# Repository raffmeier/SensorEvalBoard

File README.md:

# Sensor Evaluation Board

## Overview

These are the KiCad files for a simple sensor evaluation board. It features an STM32F4 MCU, an IMU (BMI088), a magnetometer (LIS3MDLTR) and a barometer (BMP390). All sensors are connected to the same I2C interface on the microcontroller. The board is powered by the USB-C port and can be programmed via the SWD pins which are placed on the connector to interface with an ST-LINK V3MINIE (UART1 is routed to STLINK). Additionaly the STM32 could be programmed via the USB cable in DFU mode by setting the BOOT0 jumper to high. The board features some extra GPIO (e.g. the sensor I2C bus, UART2) headers and two controllable LEDs.

## Pictures

PCB after SMD soldering.

Layout of the PCB. Build-Up: SGN-GND-3V3-SGN

## BOM
- STM32F401RCT6 (1)
- BMI088 (1)
- LIS3MDLTR (1)
- BMP390 (1)
- 10p 0603 cap (2)
- 10n 0603 cap (1)
- 100n 0603 cap (14)
- 1u 0603 cap (4)
- 4.7u 0805 cap (2)
- 10u 0805 cap (1)
- Red SMD LED 0603 (3)
- Ferrite bead 600 ohm 0805 (e.g. HZ0805E601R-10) (1)
- 100 resistor 0603 (1)
- 510 resistor 0603 (3)
- 5.1k resistor (4)
- 10k resistor 0603 (1)
- USB-C USB2.0 receptacle (e.g. USB4105-GF-A) (1)
- FTSH-107-01-L-DV-KCONN HEADER SMD 14POS 1.27MM Samtec Inc. (1)
- USB TVS diode STMicroelectronics USBLC6-2SC6 (1)
- Linear regulator SOT23-5 (e.g. MIC5504-3.3YM5-TR) (1)
- 16MHz oscillator TSX-3225 16.0000MF09Z-AC0 (1)

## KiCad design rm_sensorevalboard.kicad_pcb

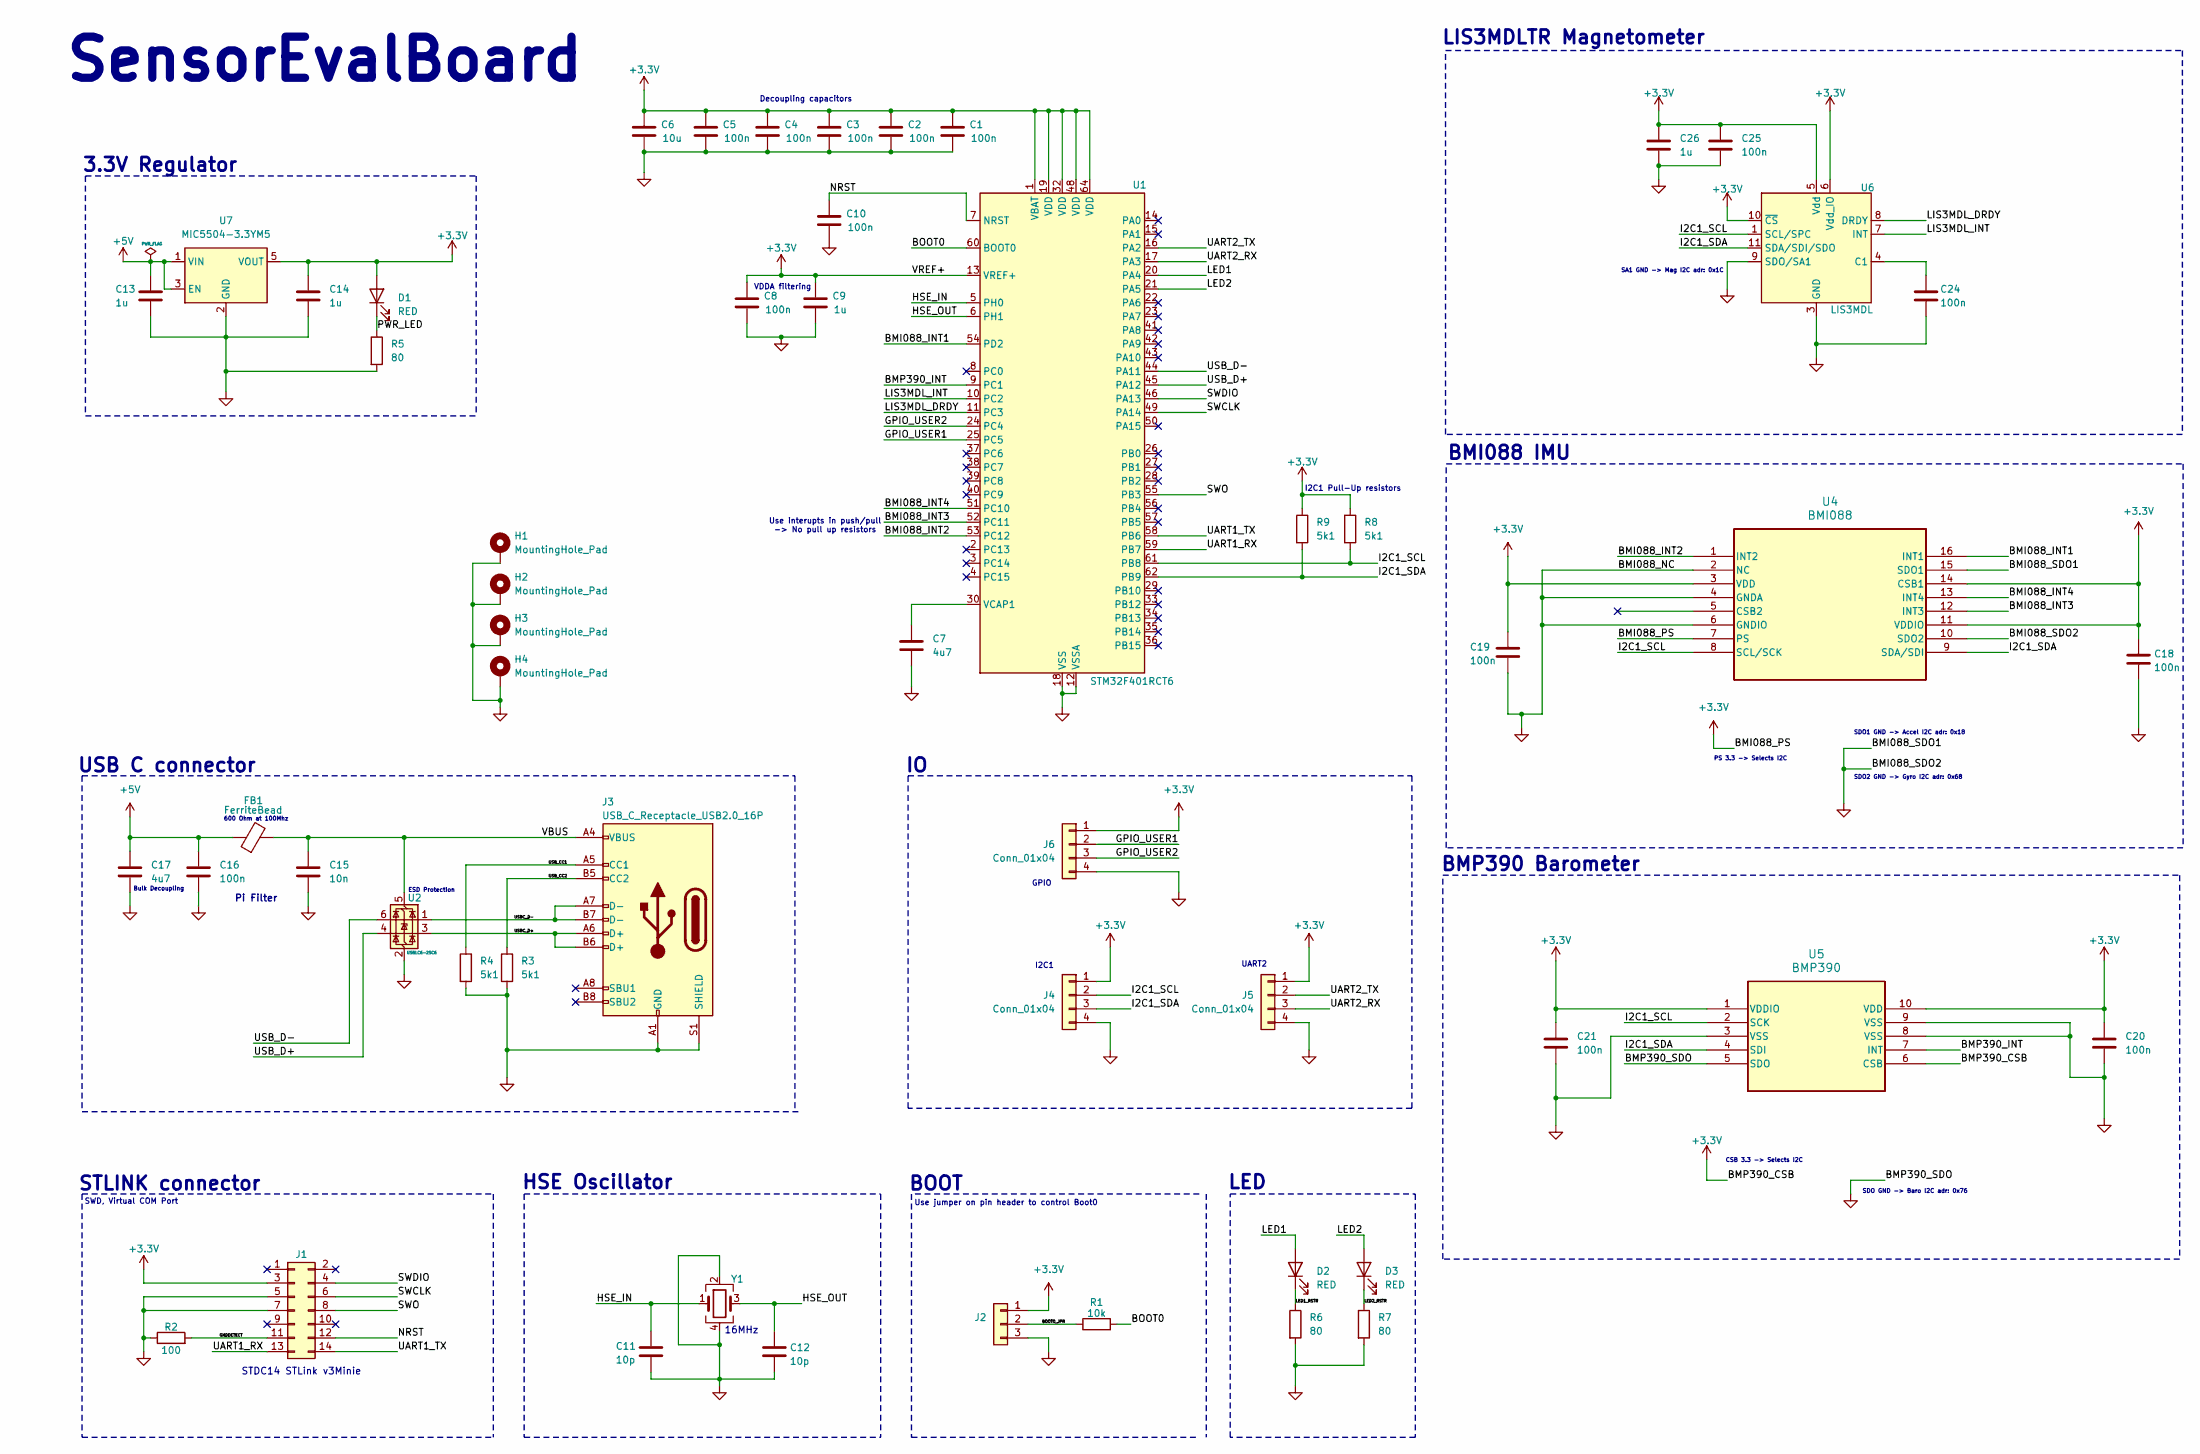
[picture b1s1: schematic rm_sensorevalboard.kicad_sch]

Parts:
C1, C2, C3, C4, C5, C8, C10, C16, C18, C19, C20, C21, C24, C25: 100n; C_0603_1608Metric
C6: 10u; C_0805_2012Metric
C7, C17: 4u7; C_0805_2012Metric
C9, C13, C14, C26: 1u; C_0603_1608Metric
C11, C12: 10p; C_0603_1608Metric
C15: 10n; C_0603_1608Metric
D1, D2, D3: RED; LED_0603_1608Metric; LCSC Part # C2286
FB1: FerriteBead; L_0805_2012Metric; LCSC Part # C1017
H1, H2, H3, H4: MountingHole_Pad; MountingHole_3.2mm_M3_Pad_Via
J1: Conn_02x07_Odd_Even; SAMTEC_FTSH-107-01-F-DV-K; LCSC Part # C7465995
J2: Conn_01x03; PinHeader_1x03_P2.54mm_Vertical
J3: USB_C_Receptacle_USB2.0_16P; USB_C_Receptacle_G-Switch_GT-USB-7010ASV; LCSC Part # C393939
J4, J5, J6: Conn_01x04; PinHeader_1x04_P2.54mm_Vertical
R1: 10k; R_0603_1608Metric
R2: 100; R_0603_1608Metric
R3, R4, R8, R9: 5k1; R_0603_1608Metric
R5, R6, R7: 80; R_0603_1608Metric
U1: STM32F401RCT6; LQFP-64_10x10mm_P0.5mm; LCSC Part # C74524
U2: USBLC6-2SC6; SOT-23-6
U4: BMI088; QFN_BMI085_BOS; LCSC Part # C194919
U5: BMP390; LCSC Part # C2684802
U6: LIS3MDL; LGA-12_2x2mm_P0.5mm
U7: MIC5504-3.3YM5; SOT-23-5
Y1: Crystal_GND24; Crystal_SMD_3225-4Pin_3.2x2.5mm; LCSC Part # C13738

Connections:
+3.3V: C1.1, C2.1, C3.1, C4.1, C5.1, C6.1, C8.1, C9.1, C14.1, C18.1, C19.1, C20.1, C21.1, C25.1, C26.1, D1.2 (A), J1.3, J2.1, J4.1, J5.1, J6.1, R8.1, R9.1, U1.1 (VBAT), U1.13 (VREF+), U1.19 (VDD), U1.32 (VDD), U1.48 (VDD), U1.64 (VDD), U4.3 (VDD), U4.7 (PS), U4.11 (VDDIO), U4.14 (CSB1), U5.1 (VDDIO), U5.6 (CSB), U5.10 (VDD), U6.5 (Vdd), U6.6 (Vdd_IO), U6.10 (~CS), U7.5 (VOUT)
+5V: C13.1, C16.1, C17.1, FB1.1, U7.1 (VIN), U7.3 (EN)
/BMI088_INT1: U1.54 (PD2), U4.16 (INT1)
/BMI088_INT2: U1.53 (PC12), U4.1 (INT2)
/BMI088_INT3: U1.52 (PC11), U4.12 (INT3)
/BMI088_INT4: U1.51 (PC10), U4.13 (INT4)
/BMP390_INT: U1.9 (PC1), U5.7 (INT)
/BOOT0: R1.2, U1.60 (BOOT0)
/BOOT0_JPR: J2.2, R1.1
/GNDDETECT: J1.11, R2.2
/GPIO_USER1: J6.2, U1.25 (PC5)
/GPIO_USER2: J6.3, U1.24 (PC4)
/HSE_IN: C11.1, U1.5 (PH0), Y1.1
/HSE_OUT: C12.1, U1.6 (PH1), Y1.3
/I2C1_SCL: J4.2, R8.2, U1.61 (PB8), U4.8 (SCL/SCK), U5.2 (SCK), U6.1 (SCL/SPC)
/I2C1_SDA: J4.3, R9.2, U1.62 (PB9), U4.9 (SDA/SDI), U5.4 (SDI), U6.11 (SDA/SDI/SDO)
/LED1: D2.2 (A), U1.20 (PA4)
/LED1_RSTR: D2.1 (K), R6.1
/LED2: D3.2 (A), U1.21 (PA5)
/LED2_RSTR: D3.1 (K), R7.1
/LIS3MDL_DRDY: U1.11 (PC3), U6.8 (DRDY)
/LIS3MDL_INT: U1.10 (PC2), U6.7 (INT)
/NRST: C10.1, J1.12, U1.7 (NRST)
/PWR_LED: D1.1 (K), R5.1
/SWCLK: J1.6, U1.49 (PA14)
/SWDIO: J1.4, U1.46 (PA13)
/SWO: J1.8, U1.55 (PB3)
/UART1_RX: J1.13, U1.59 (PB7)
/UART1_TX: J1.14, U1.58 (PB6)
/UART2_RX: J5.3, U1.17 (PA3)
/UART2_TX: J5.2, U1.16 (PA2)
/USBC_D+: J3.A6 (D+), J3.B6 (D+), U2.3 (I/O2)
/USBC_D-: J3.A7 (D-), J3.B7 (D-), U2.1 (I/O1)
/USB_CC1: J3.A5 (CC1), R4.1
/USB_CC2: J3.B5 (CC2), R3.1
/USB_D+: U1.45 (PA12), U2.4 (I/O2)
/USB_D-: U1.44 (PA11), U2.6 (I/O1)
/VBUS: C15.1, FB1.2, J3.A4 (VBUS), J3.A9 (VBUS), J3.B4 (VBUS), J3.B9 (VBUS), U2.5 (VBUS)
GND: C1.2, C2.2, C3.2, C4.2, C5.2, C6.2, C7.2, C8.2, C9.2, C10.2, C11.2, C12.2, C13.2, C14.2, C15.2, C16.2, C17.2, C18.2, C19.2, C20.2, C21.2, C24.2, C25.2, C26.2, H1.1, H2.1, H3.1, H4.1, J1.5, J1.7, J2.3, J3.A1 (GND), J3.A12 (GND), J3.B1 (GND), J3.B12 (GND), J3.S1 (SHIELD), J4.4, J5.4, J6.4, R2.1, R3.2, R4.2, R5.2, R6.2, R7.2, U1.12 (VSSA), U1.18 (VSS), U1.31 (VSS), U1.47 (VSS), U1.63 (VSS), U2.2 (GND), U4.2 (NC), U4.4 (GNDA), U4.6 (GNDIO), U4.10 (SDO2), U4.15 (SDO1), U5.3 (VSS), U5.5 (SDO), U5.8 (VSS), U5.9 (VSS), U6.2 (GND), U6.3 (GND), U6.9 (SDO/SA1), U6.12 (GND), U7.2 (GND), Y1.2, Y1.4
unnamed: C7.1, U1.30 (VCAP1)
unnamed: C24.1, U6.4 (C1)

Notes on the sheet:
SDO GND -> Baro I2C adr: 0x76
STDC14 STLink v3Minie
Decoupling capacitors
BOOT
600 Ohm at 100Mhz
LIS3MDLTR Magnetometer
I2C1
16MHz
SensorEvalBoard
STLINK connector
SDO2 GND -> Gyro I2C adr: 0x68
ESD Protection
HSE Oscillator
USB C connector
Bulk Decoupling
SDO1 GND -> Accel I2C adr: 0x18
GPIO
BMI088 IMU
VDDA filtering
BMP390 Barometer
Pi Filter
I2C1 Pull-Up resistors
SWD, Virtual COM Port
Use interupts in push/pull -> No pull up resistors
SA1 GND -> Mag I2C adr: 0x1C
UART2
CSB 3.3 -> Selects I2C
Use jumper on pin header to control Boot0
LED
3.3V Regulator
PS 3.3 -> Selects I2C

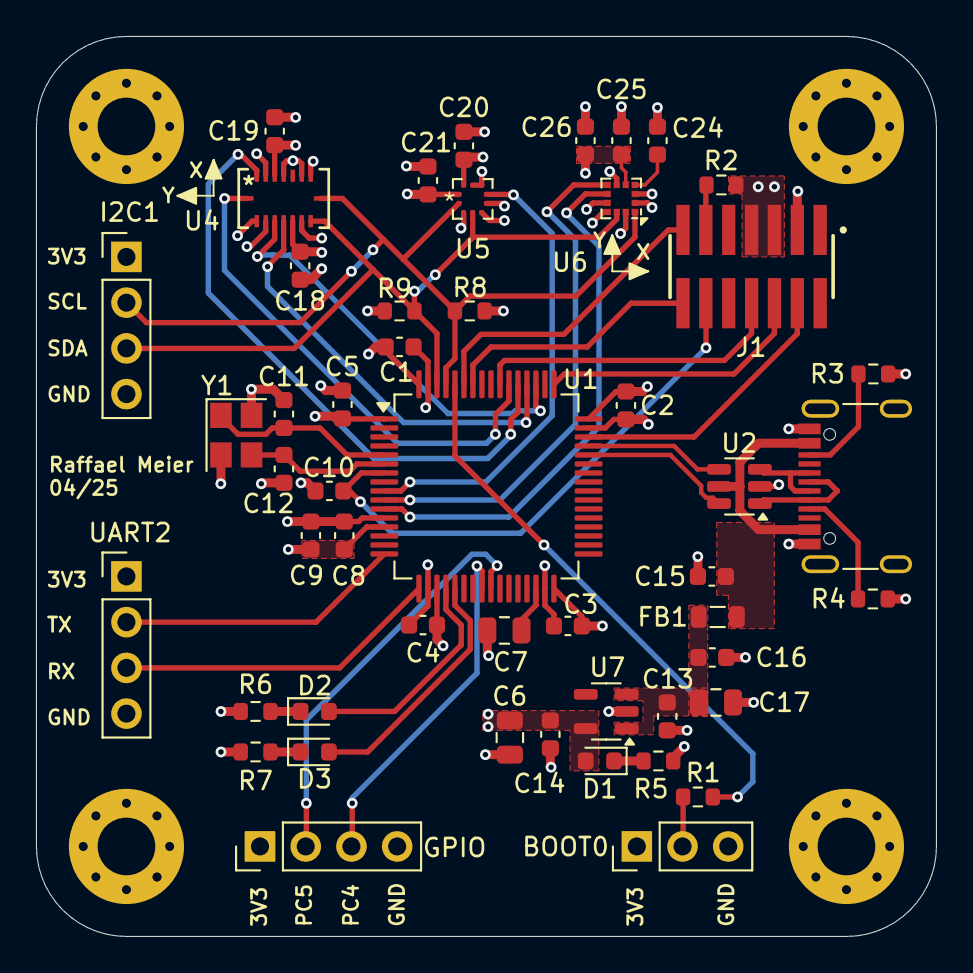
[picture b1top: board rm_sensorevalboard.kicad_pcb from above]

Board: 4 copper layers, 50.0 x 50.0 mm, 54 parts (0 on the bottom side), 41 nets.

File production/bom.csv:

Designator,Footprint,Quantity,Value,LCSC Part #
BARO,BMP390,1,BMP390,C2684802
"C1, C10, C16, C18, C19, C2, C20, C21, C24, C25, C3, C4, C5, C8",0603,14,100n,
"C11, C12",0603,2,10p,
"C13, C14, C9",0603,3,1u,
C15,0603,1,10n,
"C17, C7",0805,2,4u7,
C26,0603,1,1u,
C6,0805,1,10u,
FB1,0805,1,FerriteBead,C1017
IMU,QFN_BMI085_BOS,1,BMI088,C194919
J2,PinHeader_1x03_P2.54mm_Vertical,1,Conn_01x03,
J3,USB_C_Receptacle_G-Switch_GT-USB-7010ASV,1,USB_C_Receptacle_USB2.0_16P,C393939
"J4, J5, J6",PinHeader_1x04_P2.54mm_Vertical,3,Conn_01x04,
"LED1, LED2, PWR",0603,3,RED,C2286
MAG,LGA-12_2x2mm_P0.5mm,1,LIS3MDL,
R1,0603,1,10k,
R2,0603,1,100,
"R3, R4",0603,2,5k1,
"R5, R6, R7",0603,3,510,
"R8, R9",0603,2,4k7,
STLINK,SAMTEC_FTSH-107-01-F-DV-K,1,Conn_02x07_Odd_Even,C7465995
U1,LQFP-64_10x10mm_P0.5mm,1,STM32F401RCT6,C74524
U2,SOT-23-6,1,USBLC6-2SC6,
U3,SOT-23-3,1,XC6206P332MR-G,C5446
Y1,Crystal_SMD_3225-4Pin_3.2x2.5mm,1,Crystal_GND24,C13738

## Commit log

2025-07-26 Inital commit
2025-07-26 Remove unncessary file
2025-07-26 Update readme and add pictures
